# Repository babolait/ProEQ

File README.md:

# ProEQ

**An Arduino-based MIDI controller for precise parametric EQ VST plugin control.**

ProEQ is the hardware half of an EQ plug-in controller: a front panel of 18
absolute encoders, 15 mechanical keyswitches, 2 eleven-position rotary switches
and 270 LEDs around a 16×2 LCD, driven by its own ATmega board over MIDI. This
repository holds the KiCad sources, the shared part libraries, the
manufacturing data and the CAD sources. Fabrication packages and heavy 3D data
are published as GitHub Release assets rather than committed.

*Render of the panel as designed, not of a finished build: 5 bands × (gain,
bandwidth, frequency) with LED rings, the band on/off keyswitches, the two
11-position rotaries and the 16×2 LCD.*

## Hardware at a glance

| Block | Part | Qty | Bus |
|-------|------|-----|-----|
| MCU | Arduino / ATmega328 + USB-serial | 1 | — |
| LED driver | IS31FL3743A (36×11 matrix, 8-bit PWM per dot) | 2 | I2C, 0x20 and 0x23 |
| LEDs | 270 total (encoder value rings, switch backlight, VU) | 270 | via the 2 drivers |
| I/O expander | MCP23S17 (16 inputs each, pull-ups off, interrupts off) | 10 | SPI |
| Encoders | Bourns ACE-128 absolute (8-bit gray code) | 18 | through the expanders |
| Keyswitches | Matias Quiet Click + per-switch LED | 15 | through the expanders |
| Rotary switch | EAW 11-position, read as a resistor ladder | 2 | analog A0 / A1 |
| Light guides | VLP-450-R LED-to-frontplate optics | 270 | — |
| Display | 16×2 character LCD (HD44780, parallel) | 1 | 4-bit parallel |

MCP23S17 addressing: U2–U9 on `CS_0` with A2A1A0 = 000…111, U10 on `CS_1` = 001,
U11 on `CS_1` = 000. The encoder → expander port map and the switch → expander
bit map are written down in [`docs/wiring-map.txt`](docs/wiring-map.txt) and
mirrored in `encoderMCP[]` / `encoderReg[]` / `switchMCP[]` / `switchBit[]` in
[`firmware/ProEQ/SPI_functions.h`](firmware/ProEQ/SPI_functions.h). The two agree.

## Repository layout

The KiCad project sits at the repository root so that `${KIPRJMOD}` stays short
and every library path in the design is relative to the repo.

```
ProEQ.kicad_pro / .kicad_sch / .kicad_pcb   main board (current 4-layer re-spin)
fp-lib-table, sym-lib-table                 project library tables
schematics/                                 11 sub-sheets of the main board
libraries/
  symbols/ProEQ.kicad_sym                   project symbols
  symbols/vendor/                           per-part symbol originals as imported
  footprints/ProEQ.pretty/                  project footprints
  3dmodels/                                 STEP/STP models referenced by the footprints
daughterboard/                              switch spacer board (V2, current)
firmware/ProEQ/                             Arduino sketch (same name as its folder)
manufacturing/                              BOM revisions, interactive BOMs, panel cut files
mechanical/                                 FreeCAD/STEP sources for the front plate and VU
docs/                                       printed schematics, wiring maps, photos, V1 issues
archive/                                    superseded projects and libraries, kept for history
tools/check_kicad_integrity.py              static check that nothing dangles
```

The mapping from the previous layout to this one is written down in
[`docs/repository-layout.md`](docs/repository-layout.md).

## Schematic and board

- Root sheet with 11 sub-sheets: `Power supply`, `MCU and peripherals`,
  `LED driver 1`, `LED driver 2`, `I/O expander 1`…`5`, `Keyswitches`,
  `Mechanical`. 12 printed pages, exported to
  [`docs/Schematics.pdf`](docs/Schematics.pdf).
- The sub-sheet names describe function, not part numbers: the expanders are
  MCP23S17 (SPI), and the sheets are no longer named after the I2C MCP23017.
- Main board: 4 copper layers (F.Cu, In1 = "Power", In2 = "Gnd", B.Cu),
  1.6 mm, A2 sheet, KiCad 9 format (`version 20241229`).
- Root title block still carries the original French annotations
  (`Schéma général`, `ProEQ : PCB 1`, rev 3, 2024-08-18). File, folder and sheet
  names are English; the title block was left as the board's documented
  identity. Change it in the schematic if you want it consistent.

## Opening in KiCad

Requires **KiCad 9** — verified with `kicad-cli` 9.0.2 where the repo was
assembled. The sources are KiCad 9 format (PCB `version 20241229`, schematic
`version 20250114`); KiCad 8 refuses to open them.

1. Open `ProEQ.kicad_pro`.
2. No library setup is needed: `fp-lib-table` and `sym-lib-table` point at
   `${KIPRJMOD}/libraries/...`, all committed.
3. `manufacturing/` holds what you send to a fab. There is no Gerber tree in
   git, so the fabrication-toolkit plugin
   (`fabrication-toolkit-options.json`: `AUTO TRANSLATE` and `AUTO FILL` on,
   `EXCLUDE DNP` off) regenerates the plots and the order package.

## Daughter board

`daughterboard/` is the mechanical spacer board that carries the keyswitches on
the height the front plate expects. V2 is the current version; V1 is in
`archive/daughterboard-v1/` and is only a stub schematic plus STEP/WRL exports.

## Board history

| Stage | Where | What it was |
|---|---|---|
| Fabricated V1 | not in this repo (release assets) | First board sent to fab; its fault list is in [`docs/board-v1-issues.txt`](docs/board-v1-issues.txt), kept verbatim in French |
| Protoboard | `archive/protoboard/` | Bring-up board to prove the LED ring dimensions and the IS31 LED matrix before committing to the main board |
| Current re-spin | root | 4-layer main board, rev 3 schematics, designed and priced |

Nearly the whole V1 fault list is closed and marked ✅ in that file. Still open:
no case-mounting features on the board, the daughter-board area of the 3D print
needs reworking and a press-fit test, an open question about ordering LEDs and
single-board assembly at JLC, and the changed reversed-LCD dimensions and LCD
fold.

## Firmware

`firmware/ProEQ/` is an Arduino sketch imported from the project's own working
copy and kept byte-identical to it (`.ino` md5 `42adc70a0ed5a1b0be553c089027e123`).
The folder matches the sketch name so the Arduino IDE opens it directly.

It is a working prototype, not a finished product: encoder polling over SPI,
gray-code decoding and the LED side all work, but **every `sendMidiCC()` call is
still commented out**, so as committed it sends no MIDI. The LCD/LED refresh
block also keys off a hardcoded encoder index. See
[`firmware/README.md`](firmware/README.md) for the details.

Its lasting value is the wiring map: `SPI_functions.h` is the machine-readable
description of which encoder sits on which expander port, which is why it is
cross-checked against `docs/wiring-map.txt`.

Firmware is MIT licensed; the hardware is CERN-OHL-W-2.0. See
[`LICENSES.md`](LICENSES.md).

## Not in this repository

Everything here was tracked until this layout change; these stay out of git on
purpose and are kept locally or published as release assets.

| Excluded | Why | Where |
|---|---|---|
| `datasheets/` (11 MB of vendor PDFs) | Reference material, not design source | kept on disk, gitignored |
| `private/` | Personal notes and price quotes, no technical content | kept on disk, gitignored |
| Gerbers, JLC/PCBWay packages, CPL and position files | Regenerated from the PCB | release assets |
| `*.blend`, `*.pcb3d`, assembly STL/STEP exports | Heavy 3D, regenerable | release assets |
| Enclosure body STEP, cut front plate STEP, VLP light-guide STEP | Heavy assembly geometry | release assets, see [`.kicad-integrity-ignore`](.kicad-integrity-ignore) |
| KiCad autosaves, `*-backups/`, `fp-info-cache`, `*.kicad_prl` | Per-machine noise | gitignored |

## Checking the sources

Before and after any rename, run:

```sh
python3 tools/check_kicad_integrity.py
```

It resolves every sheet file, library nickname, footprint file, symbol name and
3D model path in every project, and exits non-zero on a dangling reference.
Geometry that is deliberately not distributed is listed with a reason in
`.kicad-integrity-ignore` and reported as a known exception, not an error.

State at this commit: 0 errors, 4 known exceptions. The same check reported 46
errors before the layout change — absolute `C:/Users/user/...` and `/home/user/...`
model paths left over from two different machines, footprint libraries that
pointed at a `ProjectEQ_PROTOBOARD.pretty` that never existed, a logo footprint
referenced through a `Personal:` library that was never registered, and the
main board pulling its footprints out of the protoboard folder.

## Licence

Hardware: CERN-OHL-W-2.0 — [`LICENSE`](LICENSE).
Firmware: MIT — [`firmware/LICENSE`](firmware/LICENSE).

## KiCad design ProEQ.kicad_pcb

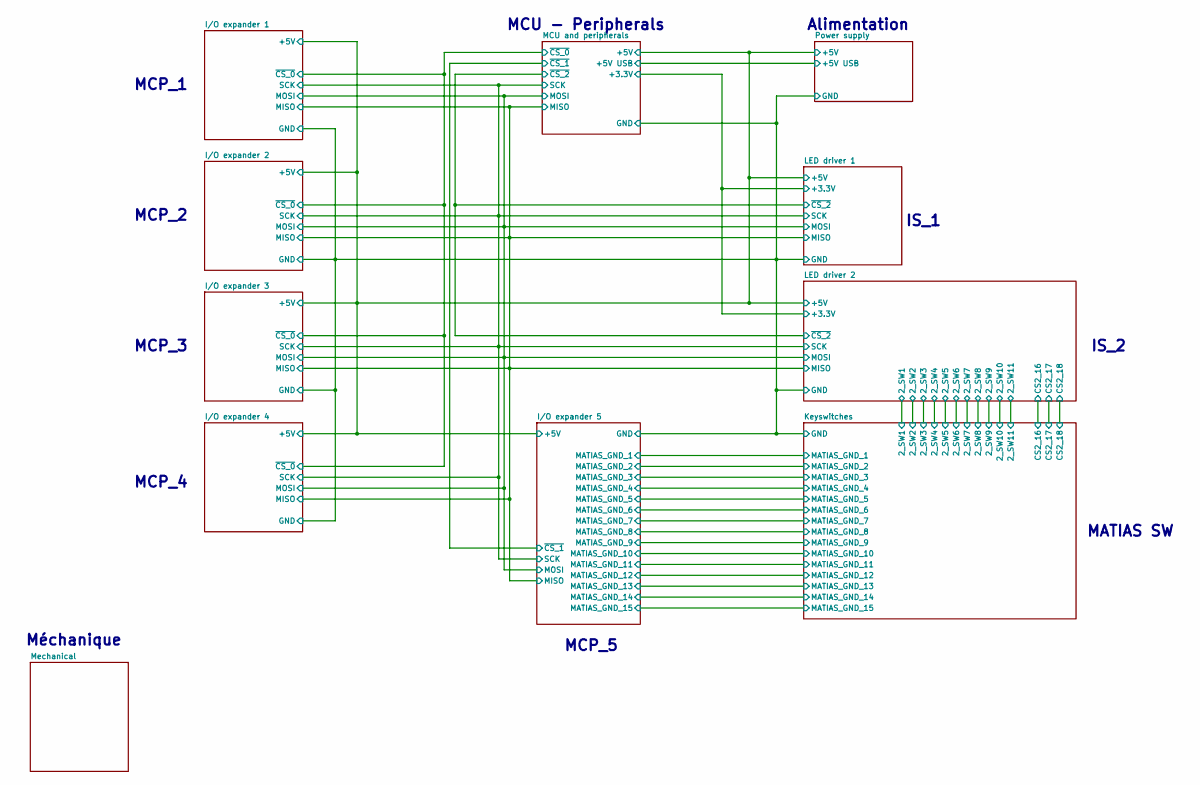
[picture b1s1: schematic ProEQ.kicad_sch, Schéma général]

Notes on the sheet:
IS_1
MCP_5
MATIAS SW
MCP_4
IS_2
MCP_1
MCU - Peripherals
Méchanique
MCP_2
MCP_3
Alimentation

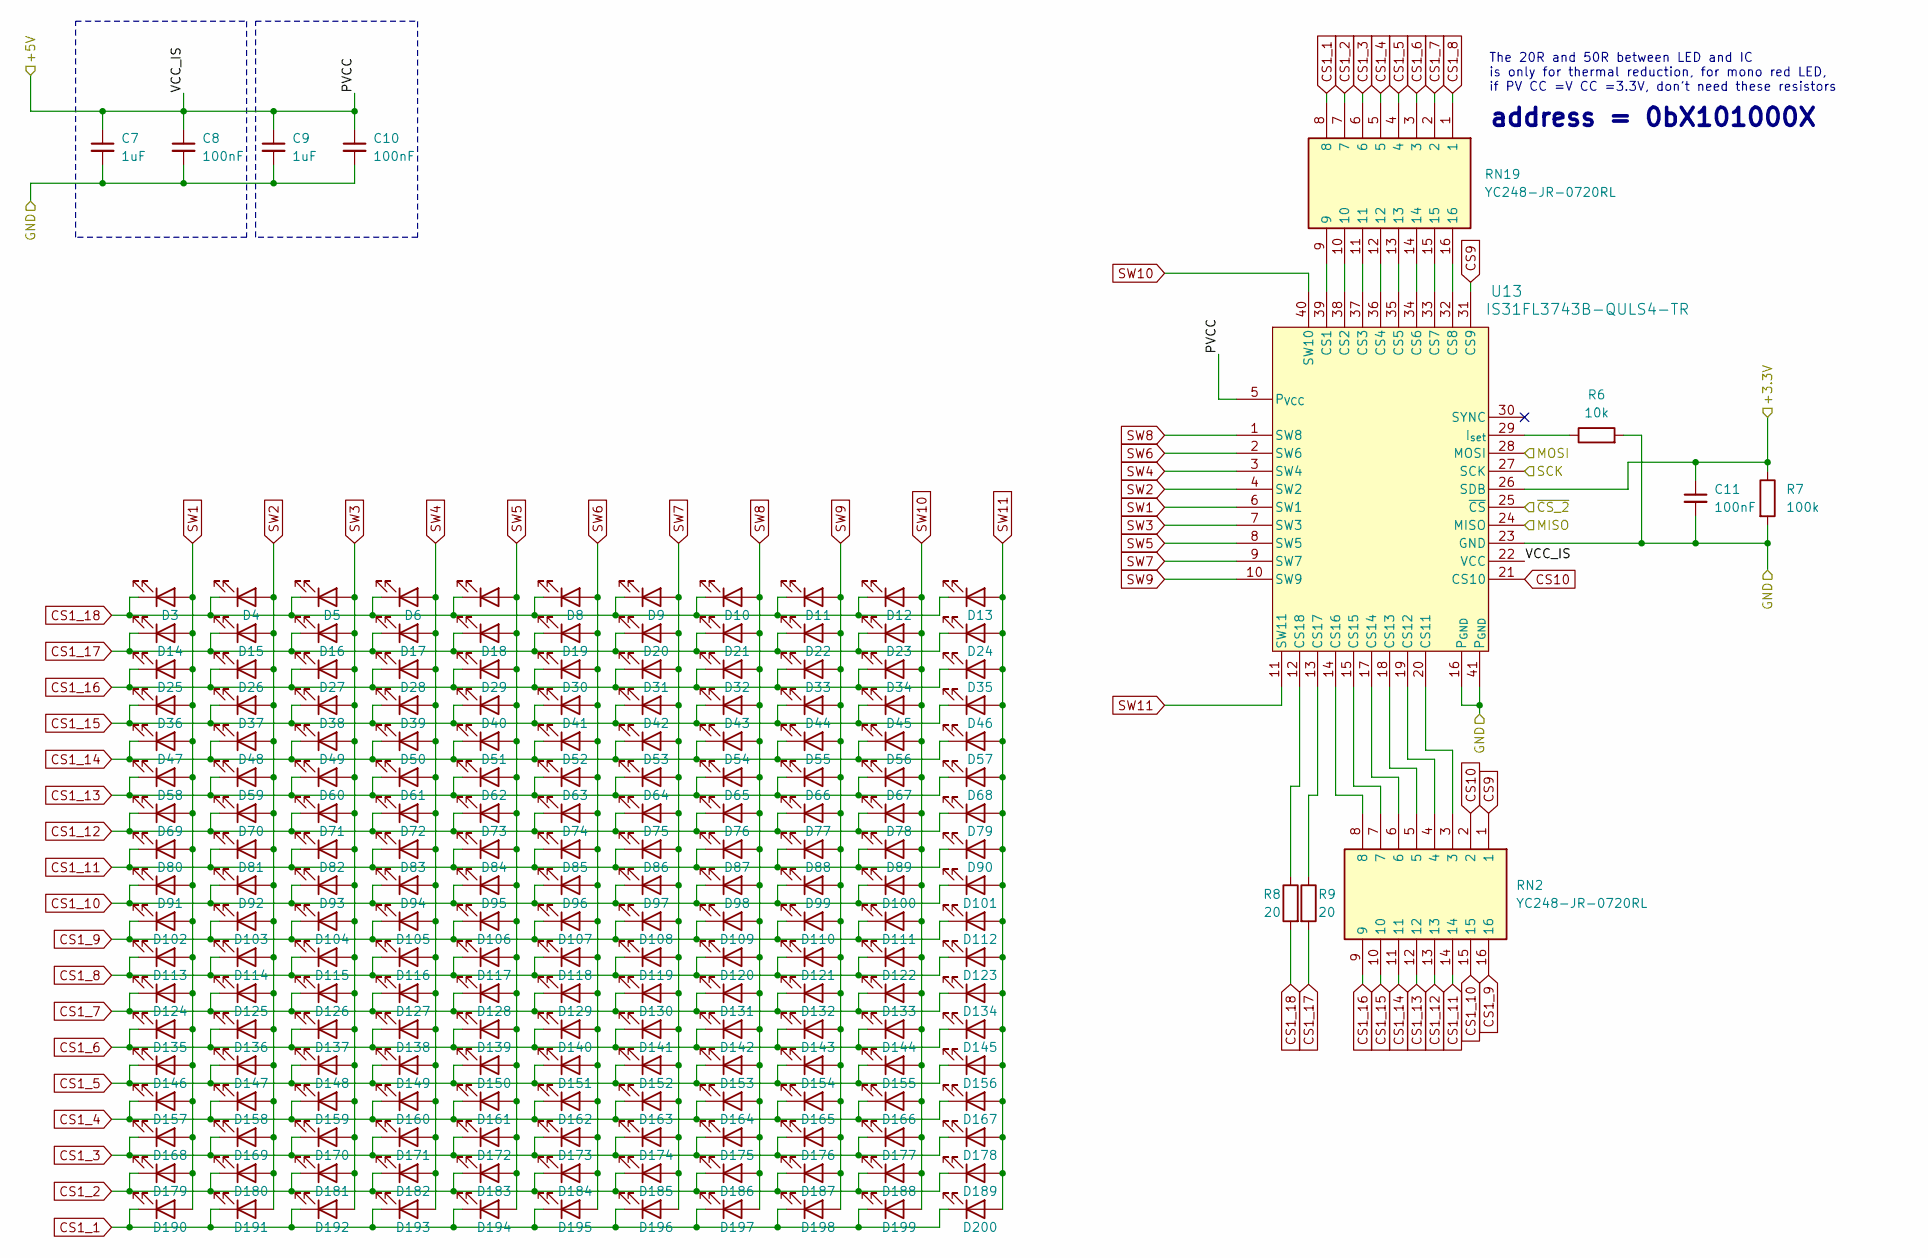
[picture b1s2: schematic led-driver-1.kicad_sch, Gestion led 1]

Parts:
C7, C9: 1uF; C_0603_1608Metric_Pad1.08x0.95mm_HandSolder; LCSC C15849
C8, C10, C11: 100nF; C_0603_1608Metric_Pad1.08x0.95mm_HandSolder; LCSC C14663
D3, D4, D5, D6, D7, D8, D9, D10, D11, D12, D13, D14, D15, D16, D17, D18, D19, D20, D21, D22, D23, D24, D25, D26, D27, D28, D29, D30, D31, D32, D33, D34, D35, D36, D37, D38, D39, D40, D41, D42, D43, D44, D45, D46, D47, D48, D49, D50, D51, D52, D53, D54, D55, D56, D57, D58, D59, D60, D61, D62, D63, D64, D65, D66, D67, D68, D69, D70, D71, D72, D73, D74, D75, D76, D77, D78, D79, D80, D81, D82, D83, D84, D85, D86, D87, D88, D89, D90, D91, D92, D93, D94, D95, D96, D97, D98, D99, D100, D101, D102, D103, D104, D105, D106, D107, D108, D109, D110, D111, D112, D113, D114, D115, D116, D117, D118, D119, D120, D121, D122, D123, D124, D125, D126, D127, D128, D129, D130, D131, D132, D133, D134, D135, D136, D137, D138, D139, D140, D141, D142, D143, D144, D145, D146, D147, D148, D149, D150, D151, D152, D153, D154, D155, D156, D157, D158, D159, D160, D161, D162, D163, D164, D165, D166, D167, D168, D169, D170, D171, D172, D173, D174, D175, D176, D177, D178, D179, D180, D181, D182, D183, D184, D185, D186, D187, D188, D189, D190, D191, D192, D193, D194, D195, D196, D197, D198, D199, D200: LED_inv; SMLZ24E2N3TT86_VLP; LCSC C20110232
R6: 10k; R_0603_1608Metric_Pad0.98x0.95mm_HandSolder; LCSC C25804
R7: 100k; R_0603_1608Metric_Pad0.98x0.95mm_HandSolder; LCSC C25803
R8, R9: 20; R_0603_1608Metric_Pad0.98x0.95mm_HandSolder; Digikey REF P20.00BYCT-ND
RN2, RN19: YC248-JR-0720RL; EXB2HV472JV; Manufacturer_Part_Number EXB-2HV472JV; Mouser Part Number 667-EXB-2HV472JV
U13: IS31FL3743B-QULS4-TR; IS31FL3743A; LCSC C2962218

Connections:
+5V: C7.1, C8.1, C9.1, C10.1, U13.5 (P_{VCC}), U13.22 (VCC); also elsewhere on the board
/IS31FL3743A1_2/+3.3V: C11.1, R7.1, U13.26 (SDB); also elsewhere on the board
/IS31FL3743A1_2/MISO: U13.24 (MISO); also elsewhere on the board
/IS31FL3743A1_2/MOSI: U13.28 (MOSI); also elsewhere on the board
/IS31FL3743A1_2/SCK: U13.27 (SCK); also elsewhere on the board
/IS31FL3743A1_2/~CS_2: U13.25 (~CS); also elsewhere on the board
CS1_1: D190.2 (K), D191.2 (K), D192.2 (K), D193.2 (K), D194.2 (K), D195.2 (K), D196.2 (K), D197.2 (K), D198.2 (K), D199.2 (K), D200.2 (K), RN19.8
CS1_2: D179.2 (K), D180.2 (K), D181.2 (K), D182.2 (K), D183.2 (K), D184.2 (K), D185.2 (K), D186.2 (K), D187.2 (K), D188.2 (K), D189.2 (K), RN19.7
CS1_3: D168.2 (K), D169.2 (K), D170.2 (K), D171.2 (K), D172.2 (K), D173.2 (K), D174.2 (K), D175.2 (K), D176.2 (K), D177.2 (K), D178.2 (K), RN19.6
CS1_4: D157.2 (K), D158.2 (K), D159.2 (K), D160.2 (K), D161.2 (K), D162.2 (K), D163.2 (K), D164.2 (K), D165.2 (K), D166.2 (K), D167.2 (K), RN19.5
CS1_5: D146.2 (K), D147.2 (K), D148.2 (K), D149.2 (K), D150.2 (K), D151.2 (K), D152.2 (K), D153.2 (K), D154.2 (K), D155.2 (K), D156.2 (K), RN19.4
CS1_6: D135.2 (K), D136.2 (K), D137.2 (K), D138.2 (K), D139.2 (K), D140.2 (K), D141.2 (K), D142.2 (K), D143.2 (K), D144.2 (K), D145.2 (K), RN19.3
CS1_7: D124.2 (K), D125.2 (K), D126.2 (K), D127.2 (K), D128.2 (K), D129.2 (K), D130.2 (K), D131.2 (K), D132.2 (K), D133.2 (K), D134.2 (K), RN19.2
CS1_8: D113.2 (K), D114.2 (K), D115.2 (K), D116.2 (K), D117.2 (K), D118.2 (K), D119.2 (K), D120.2 (K), D121.2 (K), D122.2 (K), D123.2 (K), RN19.1
CS1_9: D102.2 (K), D103.2 (K), D104.2 (K), D105.2 (K), D106.2 (K), D107.2 (K), D108.2 (K), D109.2 (K), D110.2 (K), D111.2 (K), D112.2 (K), RN2.16
CS1_10: D91.2 (K), D92.2 (K), D93.2 (K), D94.2 (K), D95.2 (K), D96.2 (K), D97.2 (K), D98.2 (K), D99.2 (K), D100.2 (K), D101.2 (K), RN2.15
CS1_11: D80.2 (K), D81.2 (K), D82.2 (K), D83.2 (K), D84.2 (K), D85.2 (K), D86.2 (K), D87.2 (K), D88.2 (K), D89.2 (K), D90.2 (K), RN2.14
CS1_12: D69.2 (K), D70.2 (K), D71.2 (K), D72.2 (K), D73.2 (K), D74.2 (K), D75.2 (K), D76.2 (K), D77.2 (K), D78.2 (K), D79.2 (K), RN2.13
CS1_13: D58.2 (K), D59.2 (K), D60.2 (K), D61.2 (K), D62.2 (K), D63.2 (K), D64.2 (K), D65.2 (K), D66.2 (K), D67.2 (K), D68.2 (K), RN2.12
CS1_14: D47.2 (K), D48.2 (K), D49.2 (K), D50.2 (K), D51.2 (K), D52.2 (K), D53.2 (K), D54.2 (K), D55.2 (K), D56.2 (K), D57.2 (K), RN2.11
CS1_15: D36.2 (K), D37.2 (K), D38.2 (K), D39.2 (K), D40.2 (K), D41.2 (K), D42.2 (K), D43.2 (K), D44.2 (K), D45.2 (K), D46.2 (K), RN2.10
CS1_16: D25.2 (K), D26.2 (K), D27.2 (K), D28.2 (K), D29.2 (K), D30.2 (K), D31.2 (K), D32.2 (K), D33.2 (K), D34.2 (K), D35.2 (K), RN2.9
CS1_17: D14.2 (K), D15.2 (K), D16.2 (K), D17.2 (K), D18.2 (K), D19.2 (K), D20.2 (K), D21.2 (K), D22.2 (K), D23.2 (K), D24.2 (K), R9.2
CS1_18: D3.2 (K), D4.2 (K), D5.2 (K), D6.2 (K), D7.2 (K), D8.2 (K), D9.2 (K), D10.2 (K), D11.2 (K), D12.2 (K), D13.2 (K), R8.2
CS9: RN2.1, U13.31 (CS9)
CS10: RN2.2, U13.21 (CS10)
GND: C7.2, C8.2, C9.2, C10.2, C11.2, R6.2, R7.2, U13.16 (P_{GND}), U13.23 (GND), U13.41 (P_{GND}); also elsewhere on the board
unnamed: RN19.9, U13.39 (CS1)
unnamed: RN19.10, U13.38 (CS2)
unnamed: RN19.11, U13.37 (CS3)
unnamed: RN19.12, U13.36 (CS4)
unnamed: RN19.13, U13.35 (CS5)
unnamed: RN19.14, U13.34 (CS6)
unnamed: RN19.15, U13.33 (CS7)
unnamed: RN19.16, U13.32 (CS8)
unnamed: RN2.3, U13.20 (CS11)
unnamed: RN2.4, U13.19 (CS12)
unnamed: RN2.5, U13.18 (CS13)
unnamed: RN2.6, U13.17 (CS14)
unnamed: RN2.7, U13.15 (CS15)
unnamed: RN2.8, U13.14 (CS16)
unnamed: R9.1, U13.13 (CS17)
unnamed: R8.1, U13.12 (CS18)
unnamed: R6.1, U13.29 (I_{set})
SW1: D3.1 (A), D14.1 (A), D25.1 (A), D36.1 (A), D47.1 (A), D58.1 (A), D69.1 (A), D80.1 (A), D91.1 (A), D102.1 (A), D113.1 (A), D124.1 (A), D135.1 (A), D146.1 (A), D157.1 (A), D168.1 (A), D179.1 (A), D190.1 (A), U13.6 (SW1)
SW2: D4.1 (A), D15.1 (A), D26.1 (A), D37.1 (A), D48.1 (A), D59.1 (A), D70.1 (A), D81.1 (A), D92.1 (A), D103.1 (A), D114.1 (A), D125.1 (A), D136.1 (A), D147.1 (A), D158.1 (A), D169.1 (A), D180.1 (A), D191.1 (A), U13.4 (SW2)
SW3: D5.1 (A), D16.1 (A), D27.1 (A), D38.1 (A), D49.1 (A), D60.1 (A), D71.1 (A), D82.1 (A), D93.1 (A), D104.1 (A), D115.1 (A), D126.1 (A), D137.1 (A), D148.1 (A), D159.1 (A), D170.1 (A), D181.1 (A), D192.1 (A), U13.7 (SW3)
SW4: D6.1 (A), D17.1 (A), D28.1 (A), D39.1 (A), D50.1 (A), D61.1 (A), D72.1 (A), D83.1 (A), D94.1 (A), D105.1 (A), D116.1 (A), D127.1 (A), D138.1 (A), D149.1 (A), D160.1 (A), D171.1 (A), D182.1 (A), D193.1 (A), U13.3 (SW4)
SW5: D7.1 (A), D18.1 (A), D29.1 (A), D40.1 (A), D51.1 (A), D62.1 (A), D73.1 (A), D84.1 (A), D95.1 (A), D106.1 (A), D117.1 (A), D128.1 (A), D139.1 (A), D150.1 (A), D161.1 (A), D172.1 (A), D183.1 (A), D194.1 (A), U13.8 (SW5)
SW6: D8.1 (A), D19.1 (A), D30.1 (A), D41.1 (A), D52.1 (A), D63.1 (A), D74.1 (A), D85.1 (A), D96.1 (A), D107.1 (A), D118.1 (A), D129.1 (A), D140.1 (A), D151.1 (A), D162.1 (A), D173.1 (A), D184.1 (A), D195.1 (A), U13.2 (SW6)
SW7: D9.1 (A), D20.1 (A), D31.1 (A), D42.1 (A), D53.1 (A), D64.1 (A), D75.1 (A), D86.1 (A), D97.1 (A), D108.1 (A), D119.1 (A), D130.1 (A), D141.1 (A), D152.1 (A), D163.1 (A), D174.1 (A), D185.1 (A), D196.1 (A), U13.9 (SW7)
SW8: D10.1 (A), D21.1 (A), D32.1 (A), D43.1 (A), D54.1 (A), D65.1 (A), D76.1 (A), D87.1 (A), D98.1 (A), D109.1 (A), D120.1 (A), D131.1 (A), D142.1 (A), D153.1 (A), D164.1 (A), D175.1 (A), D186.1 (A), D197.1 (A), U13.1 (SW8)
SW9: D11.1 (A), D22.1 (A), D33.1 (A), D44.1 (A), D55.1 (A), D66.1 (A), D77.1 (A), D88.1 (A), D99.1 (A), D110.1 (A), D121.1 (A), D132.1 (A), D143.1 (A), D154.1 (A), D165.1 (A), D176.1 (A), D187.1 (A), D198.1 (A), U13.10 (SW9)
SW10: D12.1 (A), D23.1 (A), D34.1 (A), D45.1 (A), D56.1 (A), D67.1 (A), D78.1 (A), D89.1 (A), D100.1 (A), D111.1 (A), D122.1 (A), D133.1 (A), D144.1 (A), D155.1 (A), D166.1 (A), D177.1 (A), D188.1 (A), D199.1 (A), U13.40 (SW10)
SW11: D13.1 (A), D24.1 (A), D35.1 (A), D46.1 (A), D57.1 (A), D68.1 (A), D79.1 (A), D90.1 (A), D101.1 (A), D112.1 (A), D123.1 (A), D134.1 (A), D145.1 (A), D156.1 (A), D167.1 (A), D178.1 (A), D189.1 (A), D200.1 (A), U13.11 (SW11)

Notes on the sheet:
The 20R and 50R between LED and IC is only for thermal reduction, for mono red LED, if PV CC =V CC =3.3V, don't need these resistors
address = 0bX101000X

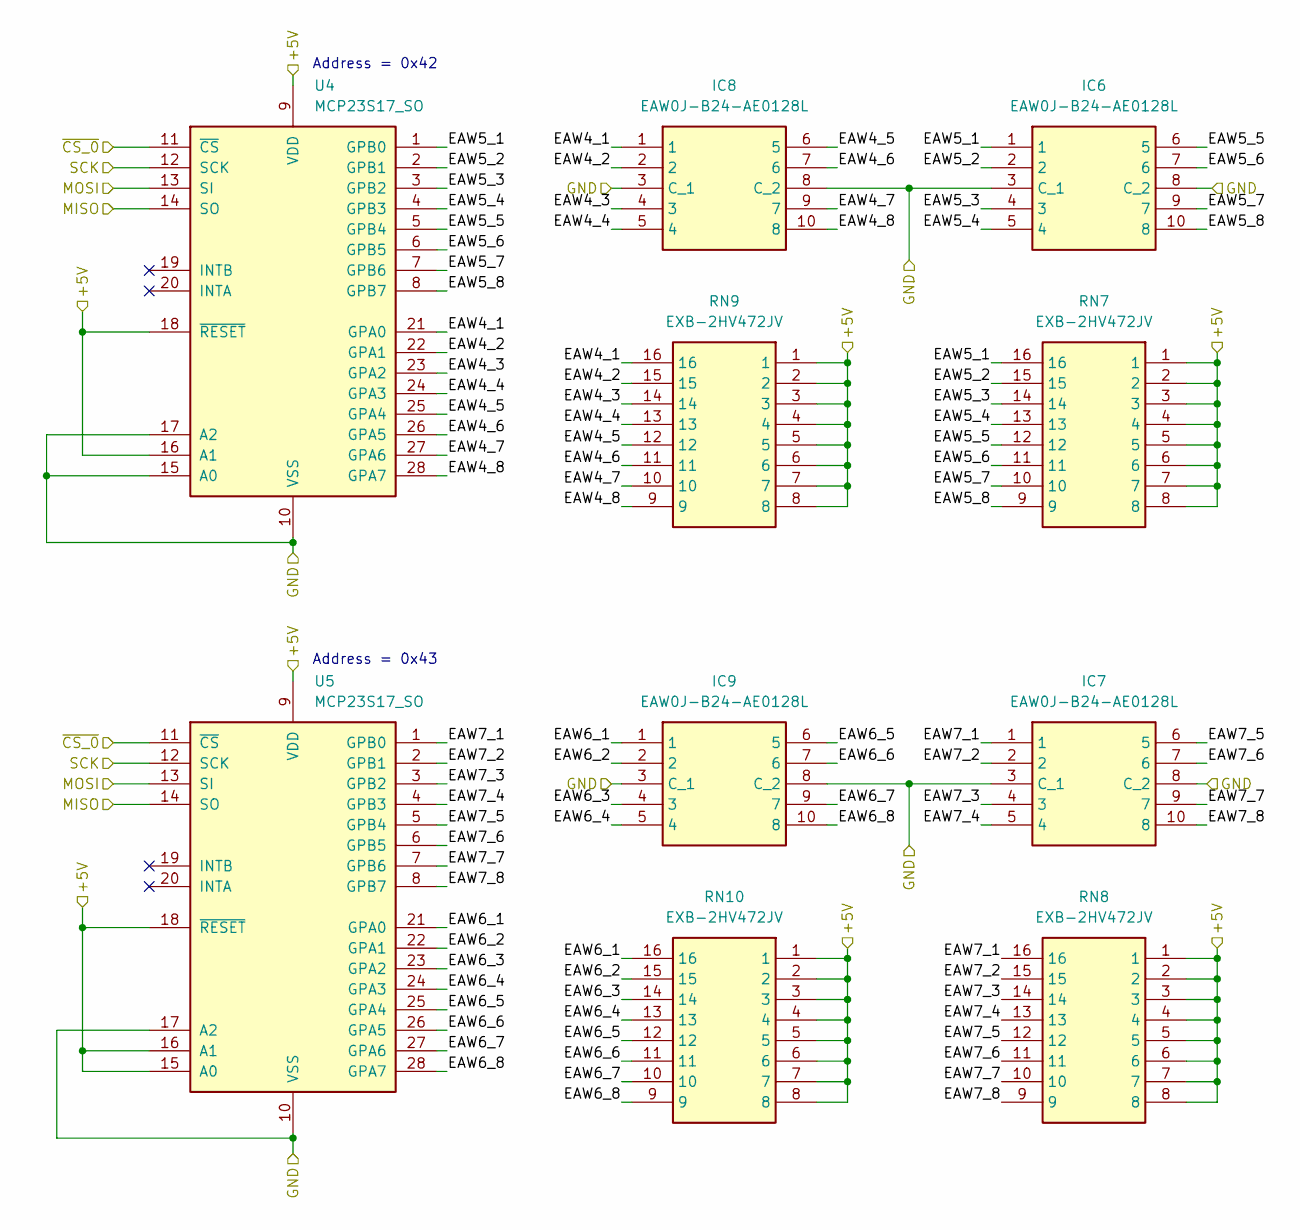
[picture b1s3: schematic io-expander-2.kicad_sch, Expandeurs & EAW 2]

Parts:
IC6, IC7, IC8, IC9: EAW0J-B24-AE0128L; Manufacturer_Part_Number EAW0J-B24-AE0128L; Mouser Part Number 652-EAW0J-B24-AEL
RN7, RN8, RN9, RN10: EXB-2HV472JV; EXB2HV472JV; Manufacturer_Part_Number EXB-2HV472JV; Mouser Part Number 667-EXB-2HV472JV
U4, U5: MCP23S17_SO; SSOP-28_5.3x10.2mm_P0.65mm; Digikey REF MCP23S17-E/SS-ND

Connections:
+5V: RN7.1, RN7.2, RN7.3, RN7.4, RN7.5, RN7.6, RN7.7, RN7.8, RN8.1, RN8.2, RN8.3, RN8.4, RN8.5, RN8.6, RN8.7, RN8.8, RN9.1, RN9.2, RN9.3, RN9.4, RN9.5, RN9.6, RN9.7, RN9.8, RN10.1, RN10.2, RN10.3, RN10.4, RN10.5, RN10.6, RN10.7, RN10.8, U4.9 (VDD), U4.16 (A1), U4.18 (~RESET), U5.9 (VDD), U5.15 (A0), U5.16 (A1), U5.18 (~RESET); also elsewhere on the board
/IS31FL3743A1_2/MISO: U4.14 (SO), U5.14 (SO); also elsewhere on the board
/IS31FL3743A1_2/MOSI: U4.13 (SI), U5.13 (SI); also elsewhere on the board
/IS31FL3743A1_2/SCK: U4.12 (SCK), U5.12 (SCK); also elsewhere on the board
/MCP23017 + EAW/~CS_0: U4.11 (~CS), U5.11 (~CS); also elsewhere on the board
/MCP23017 + EAW_1/EAW4_1: IC8.1, RN9.16, U4.21 (GPA0)
/MCP23017 + EAW_1/EAW4_2: IC8.2, RN9.15, U4.22 (GPA1)
/MCP23017 + EAW_1/EAW4_3: IC8.4 (3), RN9.14, U4.23 (GPA2)
/MCP23017 + EAW_1/EAW4_4: IC8.5 (4), RN9.13, U4.24 (GPA3)
/MCP23017 + EAW_1/EAW4_5: IC8.6 (5), RN9.12, U4.25 (GPA4)
/MCP23017 + EAW_1/EAW4_6: IC8.7 (6), RN9.11, U4.26 (GPA5)
/MCP23017 + EAW_1/EAW4_7: IC8.9 (7), RN9.10, U4.27 (GPA6)
/MCP23017 + EAW_1/EAW4_8: IC8.10 (8), RN9.9, U4.28 (GPA7)
/MCP23017 + EAW_1/EAW5_1: IC6.1, RN7.16, U4.1 (GPB0)
/MCP23017 + EAW_1/EAW5_2: IC6.2, RN7.15, U4.2 (GPB1)
/MCP23017 + EAW_1/EAW5_3: IC6.4 (3), RN7.14, U4.3 (GPB2)
/MCP23017 + EAW_1/EAW5_4: IC6.5 (4), RN7.13, U4.4 (GPB3)
/MCP23017 + EAW_1/EAW5_5: IC6.6 (5), RN7.12, U4.5 (GPB4)
/MCP23017 + EAW_1/EAW5_6: IC6.7 (6), RN7.11, U4.6 (GPB5)
/MCP23017 + EAW_1/EAW5_7: IC6.9 (7), RN7.10, U4.7 (GPB6)
/MCP23017 + EAW_1/EAW5_8: IC6.10 (8), RN7.9, U4.8 (GPB7)
/MCP23017 + EAW_1/EAW6_1: IC9.1, RN10.16, U5.21 (GPA0)
/MCP23017 + EAW_1/EAW6_2: IC9.2, RN10.15, U5.22 (GPA1)
/MCP23017 + EAW_1/EAW6_3: IC9.4 (3), RN10.14, U5.23 (GPA2)
/MCP23017 + EAW_1/EAW6_4: IC9.5 (4), RN10.13, U5.24 (GPA3)
/MCP23017 + EAW_1/EAW6_5: IC9.6 (5), RN10.12, U5.25 (GPA4)
/MCP23017 + EAW_1/EAW6_6: IC9.7 (6), RN10.11, U5.26 (GPA5)
/MCP23017 + EAW_1/EAW6_7: IC9.9 (7), RN10.10, U5.27 (GPA6)
/MCP23017 + EAW_1/EAW6_8: IC9.10 (8), RN10.9, U5.28 (GPA7)
/MCP23017 + EAW_1/EAW7_1: IC7.1, RN8.16, U5.1 (GPB0)
/MCP23017 + EAW_1/EAW7_2: IC7.2, RN8.15, U5.2 (GPB1)
/MCP23017 + EAW_1/EAW7_3: IC7.4 (3), RN8.14, U5.3 (GPB2)
/MCP23017 + EAW_1/EAW7_4: IC7.5 (4), RN8.13, U5.4 (GPB3)
/MCP23017 + EAW_1/EAW7_5: IC7.6 (5), RN8.12, U5.5 (GPB4)
/MCP23017 + EAW_1/EAW7_6: IC7.7 (6), RN8.11, U5.6 (GPB5)
/MCP23017 + EAW_1/EAW7_7: IC7.9 (7), RN8.10, U5.7 (GPB6)
/MCP23017 + EAW_1/EAW7_8: IC7.10 (8), RN8.9, U5.8 (GPB7)
GND: IC6.3 (C_1), IC6.8 (C_2), IC7.3 (C_1), IC7.8 (C_2), IC8.3 (C_1), IC8.8 (C_2), IC9.3 (C_1), IC9.8 (C_2), U4.10 (VSS), U4.15 (A0), U4.17 (A2), U5.10 (VSS), U5.17 (A2); also elsewhere on the board

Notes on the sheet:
Address = 0x43
Address = 0x42

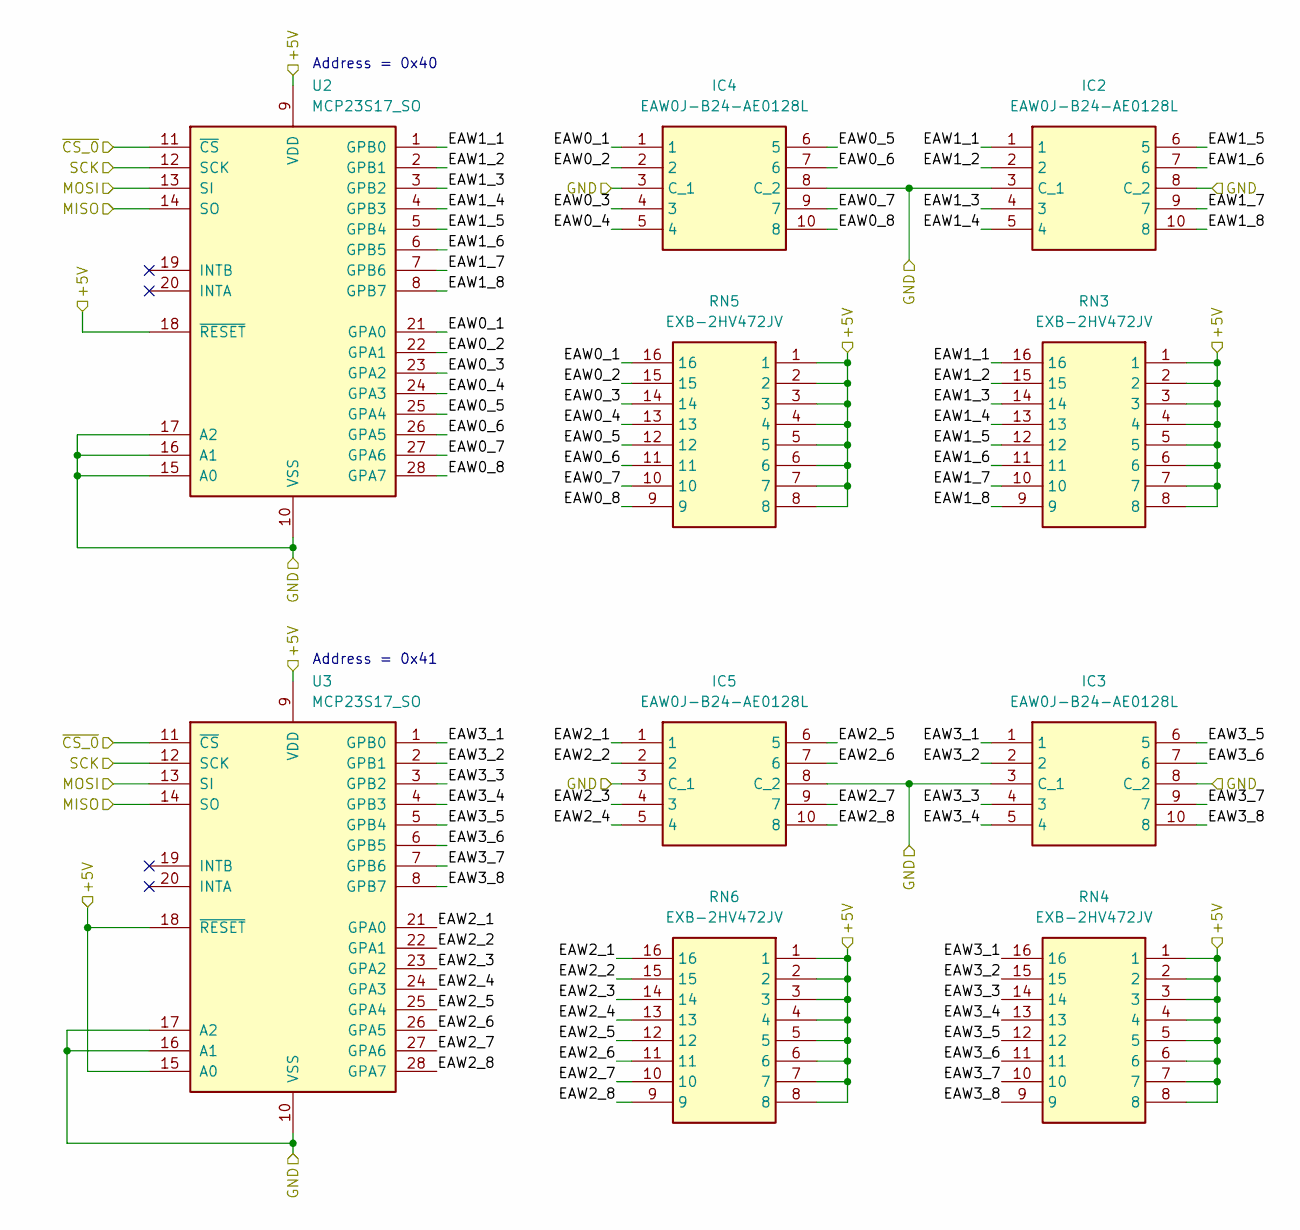
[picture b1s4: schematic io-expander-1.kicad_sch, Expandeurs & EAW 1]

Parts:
IC2, IC3, IC4, IC5: EAW0J-B24-AE0128L; Manufacturer_Part_Number EAW0J-B24-AE0128L; Mouser Part Number 652-EAW0J-B24-AEL
RN3, RN4, RN5, RN6: EXB-2HV472JV; EXB2HV472JV; Manufacturer_Part_Number EXB-2HV472JV; Mouser Part Number 667-EXB-2HV472JV
U2, U3: MCP23S17_SO; SSOP-28_5.3x10.2mm_P0.65mm; Digikey REF MCP23S17-E/SS-ND

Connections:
+5V: RN3.1, RN3.2, RN3.3, RN3.4, RN3.5, RN3.6, RN3.7, RN3.8, RN4.1, RN4.2, RN4.3, RN4.4, RN4.5, RN4.6, RN4.7, RN4.8, RN5.1, RN5.2, RN5.3, RN5.4, RN5.5, RN5.6, RN5.7, RN5.8, RN6.1, RN6.2, RN6.3, RN6.4, RN6.5, RN6.6, RN6.7, RN6.8, U2.9 (VDD), U2.18 (~RESET), U3.9 (VDD), U3.15 (A0), U3.18 (~RESET); also elsewhere on the board
/IS31FL3743A1_2/MISO: U2.14 (SO), U3.14 (SO); also elsewhere on the board
/IS31FL3743A1_2/MOSI: U2.13 (SI), U3.13 (SI); also elsewhere on the board
/IS31FL3743A1_2/SCK: U2.12 (SCK), U3.12 (SCK); also elsewhere on the board
/MCP23017 + EAW/EAW0_1: IC4.1, RN5.16, U2.21 (GPA0)
/MCP23017 + EAW/EAW0_2: IC4.2, RN5.15, U2.22 (GPA1)
/MCP23017 + EAW/EAW0_3: IC4.4 (3), RN5.14, U2.23 (GPA2)
/MCP23017 + EAW/EAW0_4: IC4.5 (4), RN5.13, U2.24 (GPA3)
/MCP23017 + EAW/EAW0_5: IC4.6 (5), RN5.12, U2.25 (GPA4)
/MCP23017 + EAW/EAW0_6: IC4.7 (6), RN5.11, U2.26 (GPA5)
/MCP23017 + EAW/EAW0_7: IC4.9 (7), RN5.10, U2.27 (GPA6)
/MCP23017 + EAW/EAW0_8: IC4.10 (8), RN5.9, U2.28 (GPA7)
/MCP23017 + EAW/EAW1_1: IC2.1, RN3.16, U2.1 (GPB0)
/MCP23017 + EAW/EAW1_2: IC2.2, RN3.15, U2.2 (GPB1)
/MCP23017 + EAW/EAW1_3: IC2.4 (3), RN3.14, U2.3 (GPB2)
/MCP23017 + EAW/EAW1_4: IC2.5 (4), RN3.13, U2.4 (GPB3)
/MCP23017 + EAW/EAW1_5: IC2.6 (5), RN3.12, U2.5 (GPB4)
/MCP23017 + EAW/EAW1_6: IC2.7 (6), RN3.11, U2.6 (GPB5)
/MCP23017 + EAW/EAW1_7: IC2.9 (7), RN3.10, U2.7 (GPB6)
/MCP23017 + EAW/EAW1_8: IC2.10 (8), RN3.9, U2.8 (GPB7)
/MCP23017 + EAW/EAW2_1: IC5.1, RN6.16, U3.21 (GPA0)
/MCP23017 + EAW/EAW2_2: IC5.2, RN6.15, U3.22 (GPA1)
/MCP23017 + EAW/EAW2_3: IC5.4 (3), RN6.14, U3.23 (GPA2)
/MCP23017 + EAW/EAW2_4: IC5.5 (4), RN6.13, U3.24 (GPA3)
/MCP23017 + EAW/EAW2_5: IC5.6 (5), RN6.12, U3.25 (GPA4)
/MCP23017 + EAW/EAW2_6: IC5.7 (6), RN6.11, U3.26 (GPA5)
/MCP23017 + EAW/EAW2_7: IC5.9 (7), RN6.10, U3.27 (GPA6)
/MCP23017 + EAW/EAW2_8: IC5.10 (8), RN6.9, U3.28 (GPA7)
/MCP23017 + EAW/EAW3_1: IC3.1, RN4.16, U3.1 (GPB0)
/MCP23017 + EAW/EAW3_2: IC3.2, RN4.15, U3.2 (GPB1)
/MCP23017 + EAW/EAW3_3: IC3.4 (3), RN4.14, U3.3 (GPB2)
/MCP23017 + EAW/EAW3_4: IC3.5 (4), RN4.13, U3.4 (GPB3)
/MCP23017 + EAW/EAW3_5: IC3.6 (5), RN4.12, U3.5 (GPB4)
/MCP23017 + EAW/EAW3_6: IC3.7 (6), RN4.11, U3.6 (GPB5)
/MCP23017 + EAW/EAW3_7: IC3.9 (7), RN4.10, U3.7 (GPB6)
/MCP23017 + EAW/EAW3_8: IC3.10 (8), RN4.9, U3.8 (GPB7)
/MCP23017 + EAW/~CS_0: U2.11 (~CS), U3.11 (~CS); also elsewhere on the board
GND: IC2.3 (C_1), IC2.8 (C_2), IC3.3 (C_1), IC3.8 (C_2), IC4.3 (C_1), IC4.8 (C_2), IC5.3 (C_1), IC5.8 (C_2), U2.10 (VSS), U2.15 (A0), U2.16 (A1), U2.17 (A2), U3.10 (VSS), U3.16 (A1), U3.17 (A2); also elsewhere on the board

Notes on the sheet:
Address = 0x41
Address = 0x40

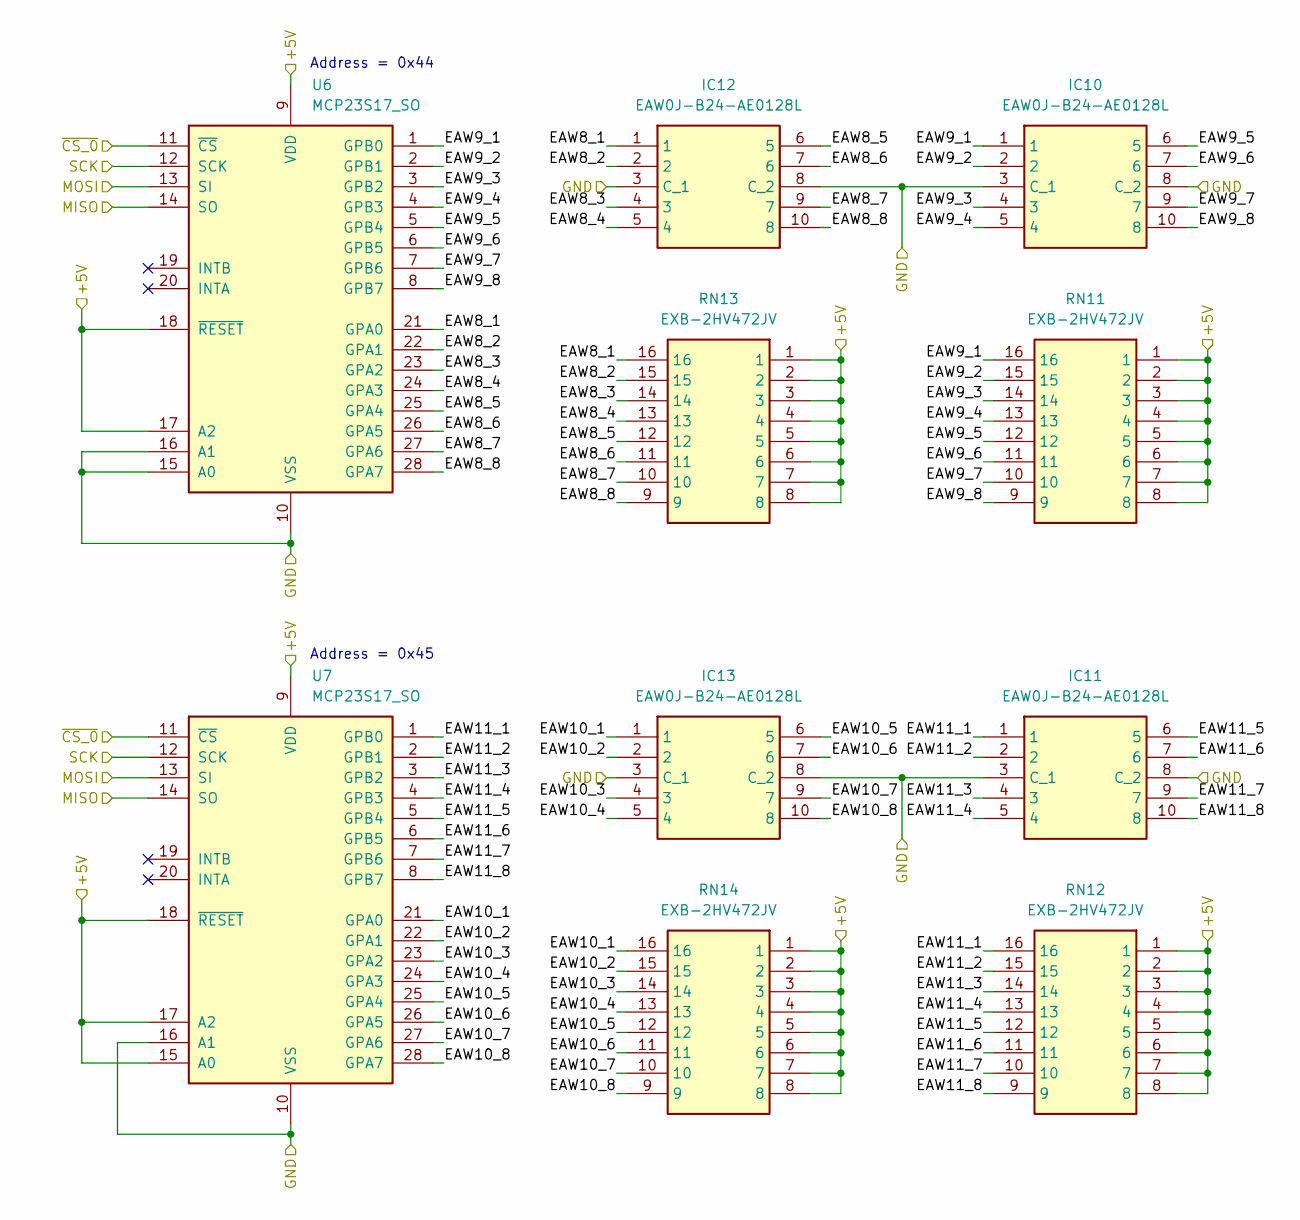
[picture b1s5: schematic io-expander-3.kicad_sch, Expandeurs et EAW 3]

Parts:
IC10, IC11, IC12, IC13: EAW0J-B24-AE0128L; Manufacturer_Part_Number EAW0J-B24-AE0128L; Mouser Part Number 652-EAW0J-B24-AEL
RN11, RN12, RN13, RN14: EXB-2HV472JV; EXB2HV472JV; Manufacturer_Part_Number EXB-2HV472JV; Mouser Part Number 667-EXB-2HV472JV
U6, U7: MCP23S17_SO; SSOP-28_5.3x10.2mm_P0.65mm; Digikey REF MCP23S17-E/SS-ND

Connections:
+5V: RN11.1, RN11.2, RN11.3, RN11.4, RN11.5, RN11.6, RN11.7, RN11.8, RN12.1, RN12.2, RN12.3, RN12.4, RN12.5, RN12.6, RN12.7, RN12.8, RN13.1, RN13.2, RN13.3, RN13.4, RN13.5, RN13.6, RN13.7, RN13.8, RN14.1, RN14.2, RN14.3, RN14.4, RN14.5, RN14.6, RN14.7, RN14.8, U6.9 (VDD), U6.17 (A2), U6.18 (~RESET), U7.9 (VDD), U7.15 (A0), U7.17 (A2), U7.18 (~RESET); also elsewhere on the board
/IS31FL3743A1_2/MISO: U6.14 (SO), U7.14 (SO); also elsewhere on the board
/IS31FL3743A1_2/MOSI: U6.13 (SI), U7.13 (SI); also elsewhere on the board
/IS31FL3743A1_2/SCK: U6.12 (SCK), U7.12 (SCK); also elsewhere on the board
/MCP23017 + EAW/~CS_0: U6.11 (~CS), U7.11 (~CS); also elsewhere on the board
/MCP23017 + EAW_2/EAW8_1: IC12.1, RN13.16, U6.21 (GPA0)
/MCP23017 + EAW_2/EAW8_2: IC12.2, RN13.15, U6.22 (GPA1)
/MCP23017 + EAW_2/EAW8_3: IC12.4 (3), RN13.14, U6.23 (GPA2)
/MCP23017 + EAW_2/EAW8_4: IC12.5 (4), RN13.13, U6.24 (GPA3)
/MCP23017 + EAW_2/EAW8_5: IC12.6 (5), RN13.12, U6.25 (GPA4)
/MCP23017 + EAW_2/EAW8_6: IC12.7 (6), RN13.11, U6.26 (GPA5)
/MCP23017 + EAW_2/EAW8_7: IC12.9 (7), RN13.10, U6.27 (GPA6)
/MCP23017 + EAW_2/EAW8_8: IC12.10 (8), RN13.9, U6.28 (GPA7)
/MCP23017 + EAW_2/EAW9_1: IC10.1, RN11.16, U6.1 (GPB0)
/MCP23017 + EAW_2/EAW9_2: IC10.2, RN11.15, U6.2 (GPB1)
/MCP23017 + EAW_2/EAW9_3: IC10.4 (3), RN11.14, U6.3 (GPB2)
/MCP23017 + EAW_2/EAW9_4: IC10.5 (4), RN11.13, U6.4 (GPB3)
/MCP23017 + EAW_2/EAW9_5: IC10.6 (5), RN11.12, U6.5 (GPB4)
/MCP23017 + EAW_2/EAW9_6: IC10.7 (6), RN11.11, U6.6 (GPB5)
/MCP23017 + EAW_2/EAW9_7: IC10.9 (7), RN11.10, U6.7 (GPB6)
/MCP23017 + EAW_2/EAW9_8: IC10.10 (8), RN11.9, U6.8 (GPB7)
/MCP23017 + EAW_2/EAW10_1: IC13.1, RN14.16, U7.21 (GPA0)
/MCP23017 + EAW_2/EAW10_2: IC13.2, RN14.15, U7.22 (GPA1)
/MCP23017 + EAW_2/EAW10_3: IC13.4 (3), RN14.14, U7.23 (GPA2)
/MCP23017 + EAW_2/EAW10_4: IC13.5 (4), RN14.13, U7.24 (GPA3)
/MCP23017 + EAW_2/EAW10_5: IC13.6 (5), RN14.12, U7.25 (GPA4)
/MCP23017 + EAW_2/EAW10_6: IC13.7 (6), RN14.11, U7.26 (GPA5)
/MCP23017 + EAW_2/EAW10_7: IC13.9 (7), RN14.10, U7.27 (GPA6)
/MCP23017 + EAW_2/EAW10_8: IC13.10 (8), RN14.9, U7.28 (GPA7)
/MCP23017 + EAW_2/EAW11_1: IC11.1, RN12.16, U7.1 (GPB0)
/MCP23017 + EAW_2/EAW11_2: IC11.2, RN12.15, U7.2 (GPB1)
/MCP23017 + EAW_2/EAW11_3: IC11.4 (3), RN12.14, U7.3 (GPB2)
/MCP23017 + EAW_2/EAW11_4: IC11.5 (4), RN12.13, U7.4 (GPB3)
/MCP23017 + EAW_2/EAW11_5: IC11.6 (5), RN12.12, U7.5 (GPB4)
/MCP23017 + EAW_2/EAW11_6: IC11.7 (6), RN12.11, U7.6 (GPB5)
/MCP23017 + EAW_2/EAW11_7: IC11.9 (7), RN12.10, U7.7 (GPB6)
/MCP23017 + EAW_2/EAW11_8: IC11.10 (8), RN12.9, U7.8 (GPB7)
GND: IC10.3 (C_1), IC10.8 (C_2), IC11.3 (C_1), IC11.8 (C_2), IC12.3 (C_1), IC12.8 (C_2), IC13.3 (C_1), IC13.8 (C_2), U6.10 (VSS), U6.15 (A0), U6.16 (A1), U7.10 (VSS), U7.16 (A1); also elsewhere on the board

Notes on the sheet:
Address = 0x44
Address = 0x45

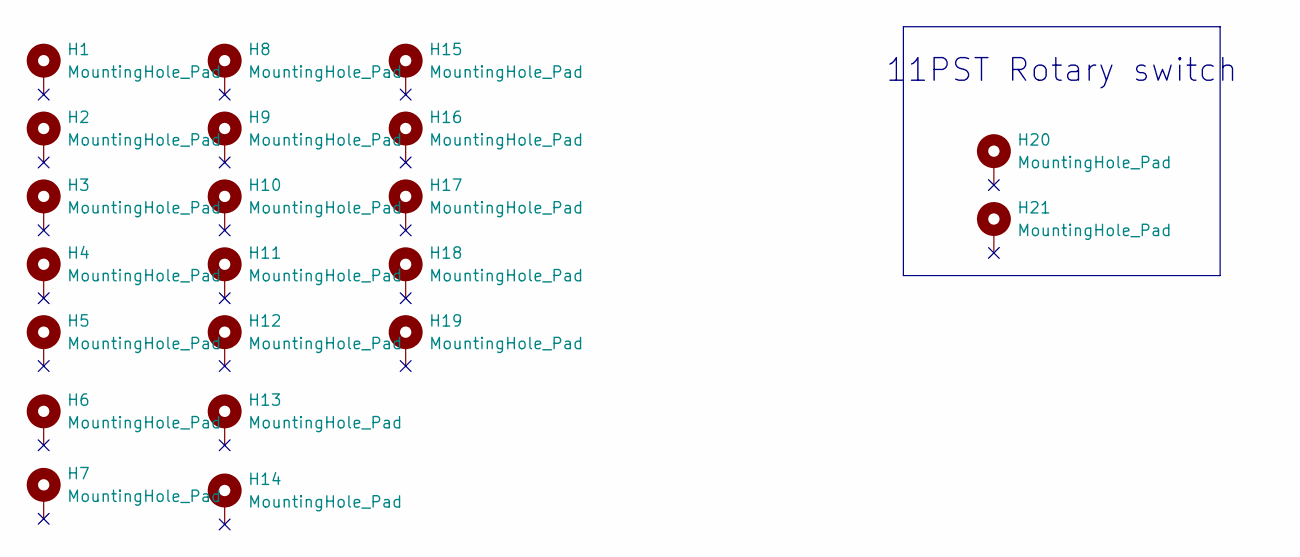
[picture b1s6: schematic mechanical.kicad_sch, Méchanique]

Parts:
H1, H2, H3, H4, H5, H6, H7, H8, H9, H10, H11, H12, H13, H14, H15, H16, H17, H18, H19: MountingHole_Pad; MountingHole_4.3mm_M4_Pad_Via
H20, H21: MountingHole_Pad; M10_1P11

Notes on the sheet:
11PST Rotary switch
